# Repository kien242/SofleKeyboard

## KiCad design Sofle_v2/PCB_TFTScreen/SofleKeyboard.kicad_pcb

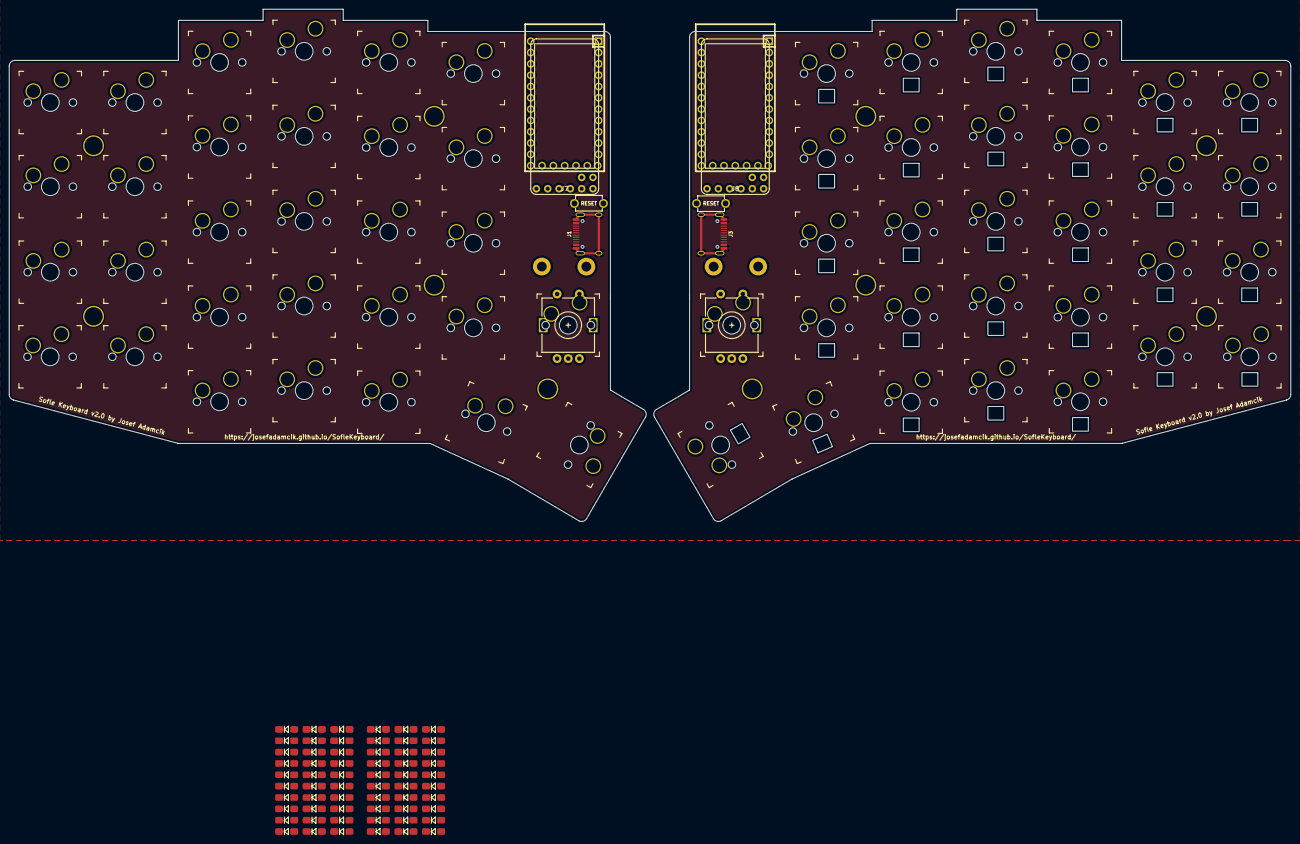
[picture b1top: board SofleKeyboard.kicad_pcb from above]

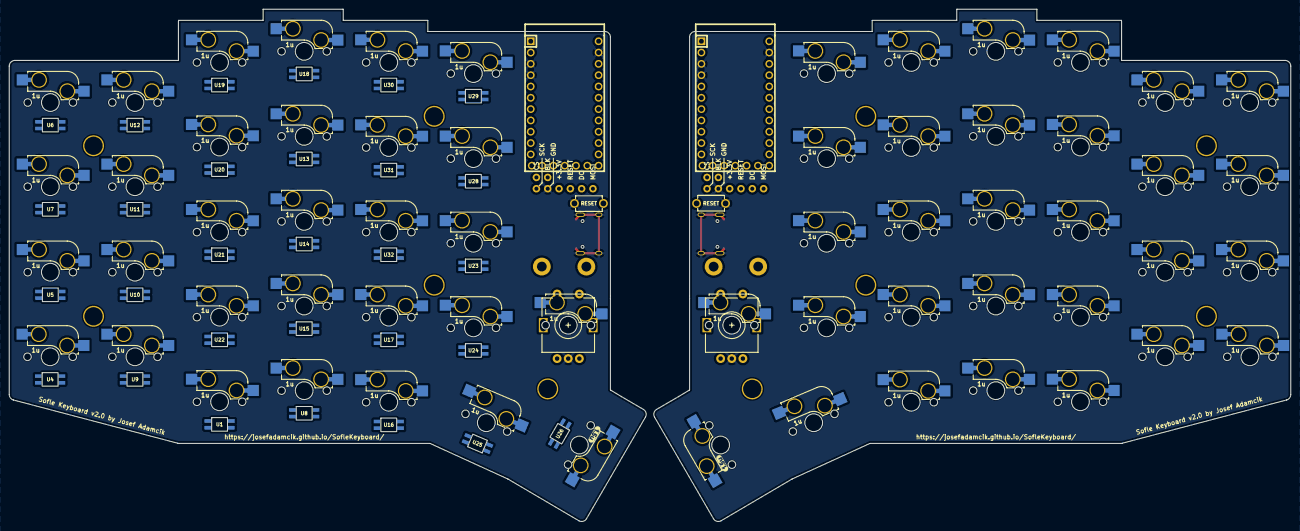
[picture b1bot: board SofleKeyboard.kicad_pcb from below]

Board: 2 copper layers, 287.8 x 115.0 mm, 173 parts (92 on the bottom side), 122 nets.

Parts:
D1, D2, D3, D4, D6, D7, D8, D9, D10, D11, D12, D13, D14, D15, D16, D17, D18, D19, D20, D21, D22, D23, D24, D25, D26, D27, D28, D29, D30, D31, D32, D33, D34, D35, D36, D37, D38, D39, D40, D41, D42, D43, D44, D45, D46, D47, D48, D49, D50, D51, D52, D53, D54, D55, D56, D57, D58, D59, D60, D61: D; Diode_SOD123_2
J1, J3: Conn_01x13; HRO-TYPE-C-31-M-12-Assembly
J7, J8: Conn_01x08; ST7735-0.96-OLED-Size
RSW1, RSW2: SW_RST; TACT_SWITCH_TVBP06
SW1, SW31: Rotary_Encoder_Switch; RotaryEncoder_Alps_EC11E-Switch_Vertical_H20mm-keebio_modif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
SW2, SW3, SW4, SW5, SW6, SW7, SW8, SW9, SW11, SW12, SW13, SW14, SW15, SW16, SW17, SW18, SW19, SW20, SW21, SW22, SW23, SW24, SW25, SW26, SW27, SW28, SW29, SW30, SW32, SW33, SW34, SW35, SW36, SW37, SW38, SW39, SW41, SW42, SW43, SW44, SW45, SW46, SW47, SW48, SW49, SW50, SW51, SW52, SW53, SW54, SW55, SW56, SW57, SW58, SW59, SW60, SW61, SW62: SW_PUSH; SW-HS-1u
SW10, SW40: SW_PUSH; SW-HS-1.5u
TH1, TH2, TH8, TH9: HOLE; M2_HOLE_PCB
TH3, TH4, TH5, TH6, TH7, TH10, TH11, TH12, TH13, TH14: HOLE; HOLE_M2_TH
U1, U4, U5, U6, U7, U8, U9, U10, U11, U12, U13, U14, U15, U16, U17, U18, U19, U20, U21, U22, U23, U24, U25, U26, U28, U29, U30, U31, U32: SK6812MINI-E
U2, U3: Elite-C

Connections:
ENCA_L: SW1.A, U2.20 (A3/PF4)
ENCA_R: SW31.A, U3.20 (A3/PF4)
ENCB_L: SW1.B, U2.19 (A2/PF5)
ENCB_R: SW31.B, U3.19 (A2/PF5)
GND: J1.1, J1.12, J1.13, J3.1, J3.12, J3.13, J7.2, J8.2, RSW1.1, RSW2.1, SW1.C, SW31.C, U1.3 (GND), U2.3 (GND), U2.4 (GND), U2.23 (GND), U3.3 (GND), U3.4 (GND), U3.23 (GND), U4.3 (GND), U5.3 (GND), U6.3 (GND), U7.3 (GND), U8.3 (GND), U9.3 (GND), U10.3 (GND), U11.3 (GND), U12.3 (GND), U13.3 (GND), U14.3 (GND), U15.3 (GND), U16.3 (GND), U17.3 (GND), U18.3 (GND), U19.3 (GND), U20.3 (GND), U21.3 (GND), U22.3 (GND), U23.3 (GND), U24.3 (GND), U25.3 (GND), U26.3 (GND), U28.3 (GND), U29.3 (GND), U30.3 (GND), U31.3 (GND), U32.3 (GND)
unnamed: D1.2 (A), SW2.2
unnamed: D2.2 (A), SW3.2
unnamed: D3.2 (A), SW4.2
unnamed: D4.2 (A), SW5.2
unnamed: D6.2 (A), SW6.2
unnamed: D7.2 (A), SW7.2
unnamed: D8.2 (A), SW8.2
unnamed: D9.2 (A), SW9.2
unnamed: D10.2 (A), SW10.2
unnamed: D11.2 (A), SW11.2
unnamed: D12.2 (A), SW12.2
unnamed: D13.2 (A), SW13.2
unnamed: D14.2 (A), SW14.2
unnamed: D15.2 (A), SW15.2
unnamed: D16.2 (A), SW16.2
unnamed: D17.2 (A), SW17.2
unnamed: D18.2 (A), SW18.2
unnamed: D19.2 (A), SW19.2
unnamed: D20.2 (A), SW20.2
unnamed: D21.2 (A), SW21.2
unnamed: D22.2 (A), SW22.2
unnamed: D23.2 (A), SW23.2
unnamed: D24.2 (A), SW24.2
unnamed: D25.2 (A), SW25.2
unnamed: D26.2 (A), SW26.2
unnamed: D27.2 (A), SW27.2
unnamed: D28.2 (A), SW28.2
unnamed: D29.2 (A), SW29.2
unnamed: D30.2 (A), SW30.2
unnamed: D31.2 (A), SW32.2
unnamed: D32.2 (A), SW33.2
unnamed: D33.2 (A), SW34.2
unnamed: D34.2 (A), SW35.2
unnamed: D36.2 (A), SW36.2
unnamed: D37.2 (A), SW37.2
unnamed: D38.2 (A), SW38.2
unnamed: D39.2 (A), SW39.2
unnamed: D40.2 (A), SW40.2
unnamed: D41.2 (A), SW41.2
unnamed: D42.2 (A), SW42.2
unnamed: D43.2 (A), SW43.2
unnamed: D44.2 (A), SW44.2
unnamed: D45.2 (A), SW45.2
unnamed: D46.2 (A), SW46.2
unnamed: D47.2 (A), SW47.2
unnamed: D48.2 (A), SW48.2
unnamed: D49.2 (A), SW49.2
unnamed: D50.2 (A), SW50.2
unnamed: D51.2 (A), SW51.2
unnamed: D52.2 (A), SW52.2
unnamed: D53.2 (A), SW53.2
unnamed: D54.2 (A), SW54.2
unnamed: D55.2 (A), SW55.2
unnamed: D56.2 (A), SW56.2
unnamed: D57.2 (A), SW57.2
unnamed: D58.2 (A), SW58.2
unnamed: D59.2 (A), SW59.2
unnamed: D60.2 (A), SW60.2
unnamed: U1.2 (DOUT), U4.4 (DIN)
unnamed: U1.1 (VDD), U4.1 (VDD), U5.1 (VDD), U6.1 (VDD), U7.1 (VDD), U8.1 (VDD), U9.1 (VDD), U10.1 (VDD), U11.1 (VDD), U12.1 (VDD), U13.1 (VDD), U14.1 (VDD), U15.1 (VDD), U16.1 (VDD), U17.1 (VDD), U18.1 (VDD), U19.1 (VDD), U20.1 (VDD), U21.1 (VDD), U22.1 (VDD), U23.1 (VDD), U24.1 (VDD), U25.1 (VDD), U26.1 (VDD), U28.1 (VDD), U29.1 (VDD), U30.1 (VDD), U31.1 (VDD), U32.1 (VDD)
unnamed: RSW1.2, U2.22 (RST)
unnamed: RSW2.2, U3.22 (RST)
unnamed: U4.2 (DOUT), U5.4 (DIN)
unnamed: U5.2 (DOUT), U7.4 (DIN)
unnamed: U6.4 (DIN), U7.2 (DOUT)
unnamed: U8.4 (DIN), U9.2 (DOUT)
unnamed: U10.4 (DIN), U11.2 (DOUT)
unnamed: U9.4 (DIN), U10.2 (DOUT)
unnamed: U11.4 (DIN), U12.2 (DOUT)
unnamed: U6.2 (DOUT), U12.4 (DIN)
unnamed: U13.4 (DIN), U18.2 (DOUT)
unnamed: U13.2 (DOUT), U14.4 (DIN)
unnamed: U14.2 (DOUT), U15.4 (DIN)
unnamed: U15.2 (DOUT), U16.4 (DIN)
unnamed: U16.2 (DOUT), U17.4 (DIN)
unnamed: U17.2 (DOUT), U32.4 (DIN)
unnamed: U18.4 (DIN), U19.2 (DOUT)
unnamed: U19.4 (DIN), U20.2 (DOUT)
unnamed: U20.4 (DIN), U21.2 (DOUT)
unnamed: U21.4 (DIN), U22.2 (DOUT)
unnamed: U8.2 (DOUT), U22.4 (DIN)
unnamed: U23.4 (DIN), U28.2 (DOUT)
unnamed: U23.2 (DOUT), U24.4 (DIN)
unnamed: U24.2 (DOUT), U25.4 (DIN)
unnamed: U25.2 (DOUT), U26.4 (DIN)
unnamed: U28.4 (DIN), U29.2 (DOUT)
unnamed: U29.4 (DIN), U30.2 (DOUT)
unnamed: U30.4 (DIN), U31.2 (DOUT)
unnamed: U31.4 (DIN), U32.2 (DOUT)
SCL_R: J8.4, U3.6 (3/PD0)
SDA_R: J8.5, U3.5 (2/PD1)
SW25A_L: SW1.S2, SW2.1, SW3.1, SW4.1, SW5.1, SW62.1, U2.13 (10/PB6)
SW25A_R: SW31.S2, SW32.1, SW33.1, SW34.1, SW35.1, SW61.1, U3.13 (10/PB6)
SW25B_L: D61.2 (A), SW1.S1, SW62.2
SW25B_R: D35.2 (A), SW31.S1, SW61.2
VCC: J7.3, U2.21 (VCC)
VDD: J8.3, U3.21 (VCC)
col0_L: SW26.1, SW27.1, SW28.1, SW29.1, SW30.1, U2.18 (A1/PF6)
col0_R: SW56.1, SW57.1, SW58.1, SW59.1, SW60.1, U3.18 (A1/PF6)
col1_L: SW21.1, SW22.1, SW23.1, SW24.1, SW25.1, U2.17 (A0/PF7)
col1_R: SW51.1, SW52.1, SW53.1, SW54.1, SW55.1, U3.17 (A0/PF7)
col2_L: SW16.1, SW17.1, SW18.1, SW19.1, SW20.1, U2.16 (15/PB1)
col2_R: SW46.1, SW47.1, SW48.1, SW49.1, SW50.1, U3.16 (15/PB1)
col3_L: SW11.1, SW12.1, SW13.1, SW14.1, SW15.1, U2.15 (14/PB3)
col3_R: SW41.1, SW42.1, SW43.1, SW44.1, SW45.1, U3.15 (14/PB3)
col4_L: SW6.1, SW7.1, SW8.1, SW9.1, SW10.1, U2.14 (16/PB2)
col4_R: SW36.1, SW37.1, SW38.1, SW39.1, SW40.1, U3.14 (16/PB2)
row0_L: D1.1 (K), D6.1 (K), D11.1 (K), D16.1 (K), D21.1 (K), D26.1 (K), U2.8 (5/PC6)
row0_R: D31.1 (K), D36.1 (K), D41.1 (K), D46.1 (K), D51.1 (K), D56.1 (K), U3.8 (5/PC6)
row1_L: D2.1 (K), D7.1 (K), D12.1 (K), D17.1 (K), D22.1 (K), D27.1 (K), U2.9 (6/PD7)
row1_R: D32.1 (K), D37.1 (K), D42.1 (K), D47.1 (K), D52.1 (K), D57.1 (K), U3.9 (6/PD7)
row2_L: D3.1 (K), D8.1 (K), D13.1 (K), D18.1 (K), D23.1 (K), D28.1 (K), U2.10 (7/PE6)
row2_R: D33.1 (K), D38.1 (K), D43.1 (K), D48.1 (K), D53.1 (K), D58.1 (K), U3.10 (7/PE6)
row3_L: D4.1 (K), D9.1 (K), D14.1 (K), D19.1 (K), D24.1 (K), D29.1 (K), U2.11 (8/PB4)
row3_R: D34.1 (K), D39.1 (K), D44.1 (K), D49.1 (K), D54.1 (K), D59.1 (K), U3.11 (8/PB4)
row4_L: D10.1 (K), D15.1 (K), D20.1 (K), D25.1 (K), D30.1 (K), D61.1 (K), U2.12 (9/PB5)
row4_R: D35.1 (K), D40.1 (K), D45.1 (K), D50.1 (K), D55.1 (K), D60.1 (K), U3.12 (9/PB5)

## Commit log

2023-05-22 Update file
